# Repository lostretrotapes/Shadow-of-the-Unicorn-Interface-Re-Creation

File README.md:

# Shadow-of-the-Unicorn-Interface-Re-Creation

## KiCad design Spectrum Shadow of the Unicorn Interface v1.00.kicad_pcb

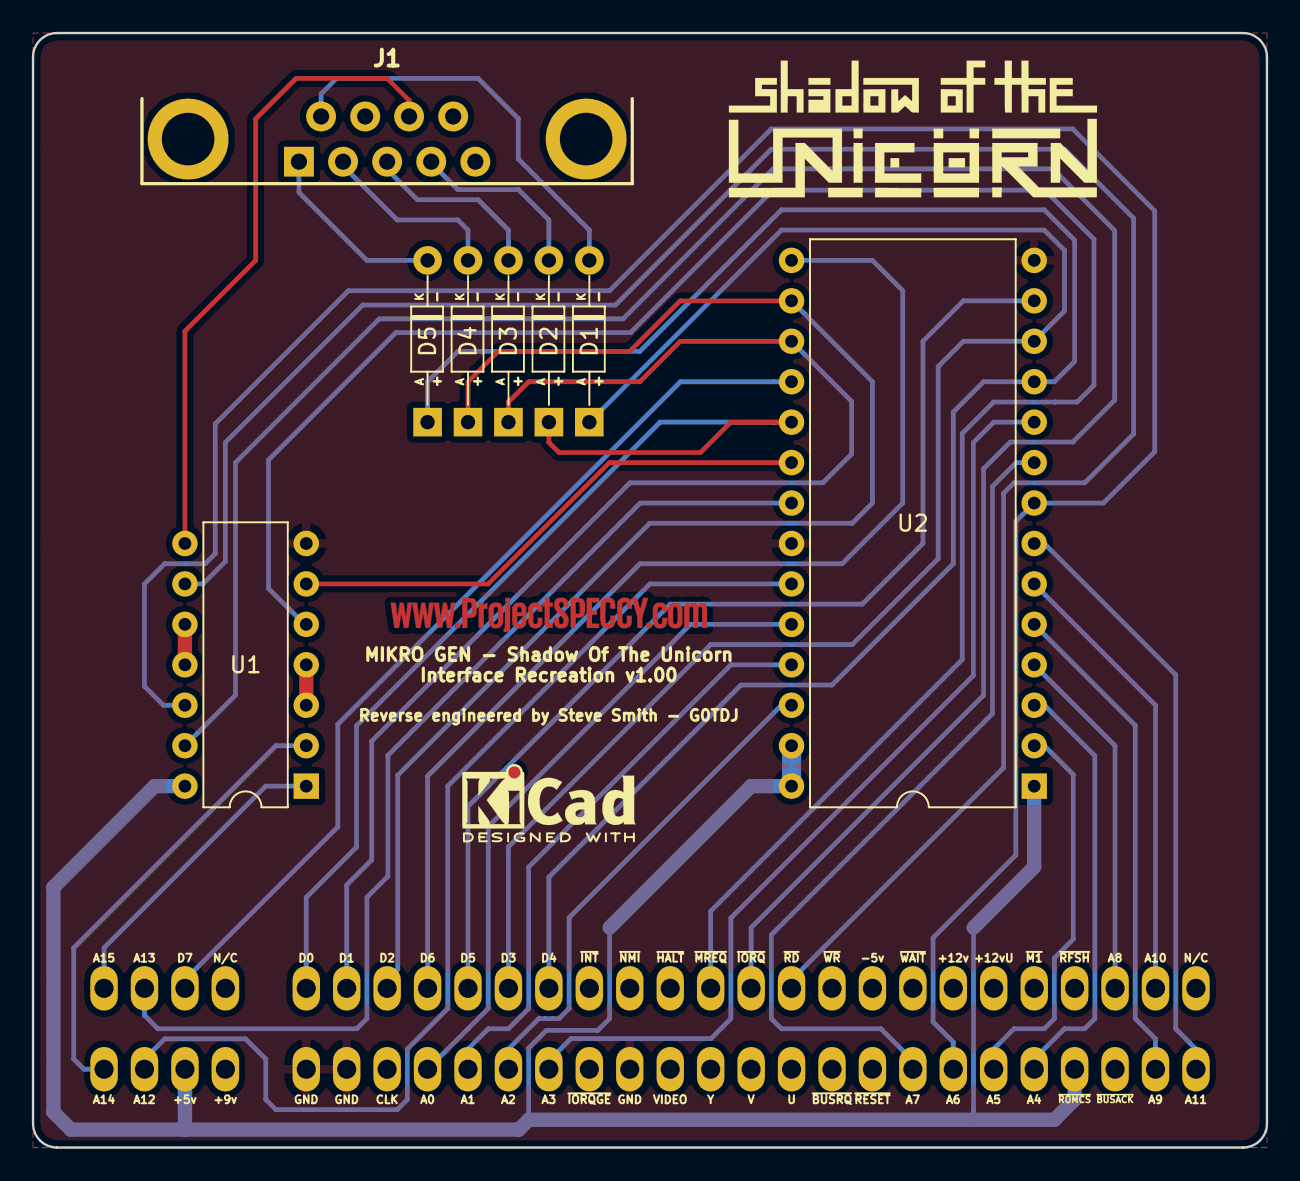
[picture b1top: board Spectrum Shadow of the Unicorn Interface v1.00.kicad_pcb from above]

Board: 2 copper layers, 77.5 x 70.0 mm, 9 parts (0 on the bottom side), 38 nets.

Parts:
D1, D2, D3, D4, D5: DIODE; 1N4001_Diode_Case_59-10_Axial
J1: DB9; SparkFun-Connectors-DB9
P1: SPECTRUM_EDGE-28x2; Spectrum_Edge_Connector
U1: 74LS32; DIP-14_W7.62mm
U2: 27C128; DIP-28_W15.24mm

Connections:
+5volts: P1.3B, P1.25B, U1.14, U2.1, U2.27, U2.28
A0: P1.9B, U2.24
A1: P1.10B, U2.25
A2: P1.11B, U2.26
A3: P1.12B, U2.10
A4: P1.24B, U2.3
A5: P1.23B, U2.2
A6: P1.22B, U1.12, U2.8
A7: P1.21B, U2.9
A8: P1.26A, U2.4
A9: P1.27B, U2.5
A10: P1.27A, U2.6
A11: P1.28B, U2.7
A12: P1.2B, U2.23
A13: P1.2A, U2.21
A14: P1.1B, U1.2
A15: P1.1A, U1.1
CE: U1.6, U2.20
D0: D2.1, P1.6A, U2.19
D1: D3.1, P1.7A, U2.17
D2: D4.1, P1.8A, U2.16
D3: D1.1, P1.11A, U2.12
D4: D5.1, P1.12A, U2.11
D5: P1.10A, U2.13
D6: P1.9A, U2.15
D7: P1.3A, U2.18
GND: P1.6B, P1.7B, P1.14B, U1.7, U2.14, U2.22
unnamed: D1.2, J1.6
unnamed: D2.2, J1.4
unnamed: D3.2, J1.3
unnamed: D4.2, J1.2
unnamed: D5.2, J1.1
unnamed: J1.8, U1.8
unnamed: U1.3, U1.4
unnamed: U1.10, U1.11
~IORQ: P1.17A, U1.13
~MREQ: P1.16A, U1.5
~RD: P1.18A, U1.9
